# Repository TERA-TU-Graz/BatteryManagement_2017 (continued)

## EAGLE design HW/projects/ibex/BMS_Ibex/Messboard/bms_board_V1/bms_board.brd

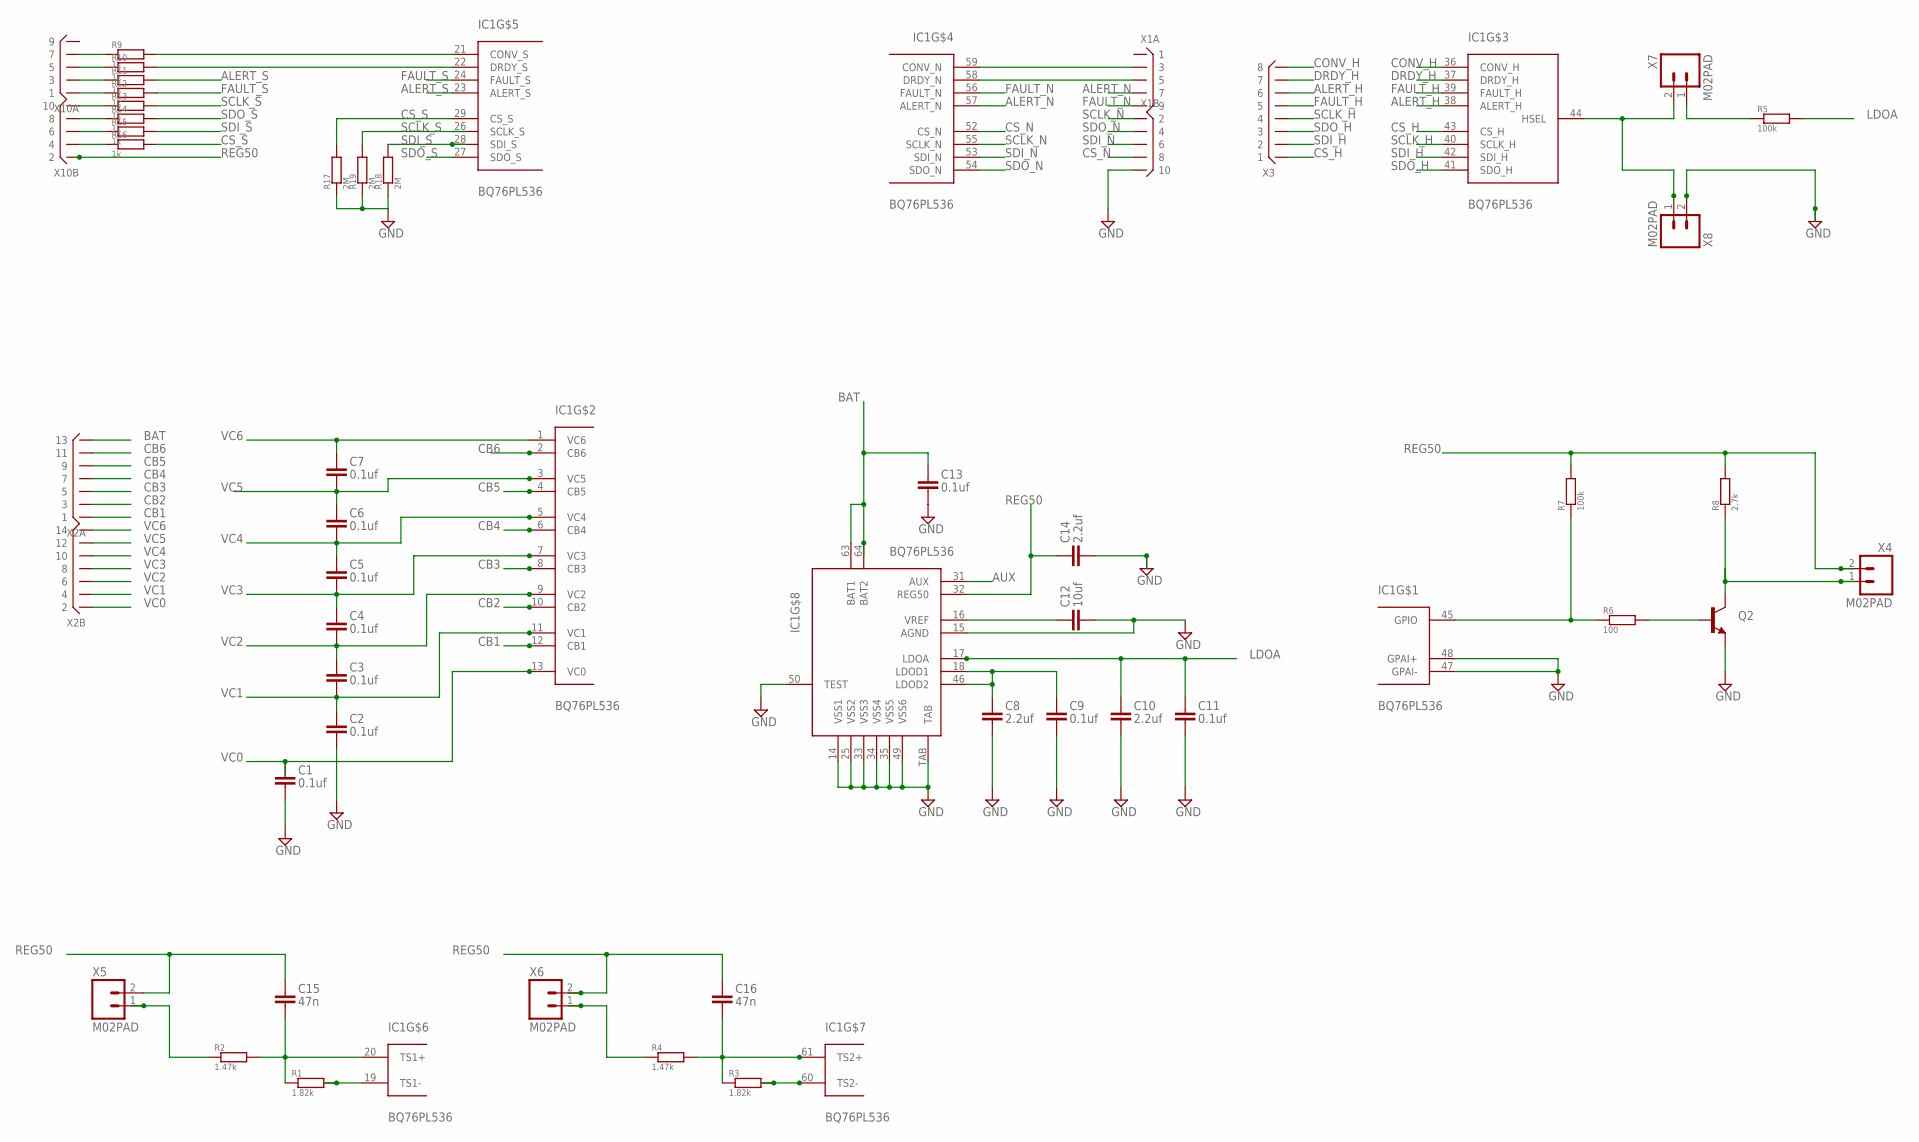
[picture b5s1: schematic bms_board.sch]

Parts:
C1, C2, C3, C4, C5, C6, C7, C9, C11, C13: 0.1uf; C0805
C8, C10, C14: 2.2uf; C0805
C12: 10uf; C0805
C15, C16: 47n; C0805
IC1: BQ76PL536; LQFP-64
Q2: TRANSISTOR_NPNSOT23; SOT23
R1, R3: 1.82k; R0805
R2, R4: 1.47k; R0805
R5, R7: 100k; R0805
R6: 100; R0805
R8: 2.7k; R0805
R9, R10, R11, R12, R13, R14, R15, R16: 1k; R0805
R17, R18, R19: 2M; R0805
X1, X10: X05X2ICR; X10ICR
X2: X07X2IR; X14R-IDC
X3: X08R; X08R-SIL
X4, X5, X6, X7, X8: M02PAD; 1X02

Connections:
ALERT_H: IC1.38 (ALERT_H), X3.6
ALERT_N: IC1.57 (ALERT_N), X1.7
ALERT_S: IC1.23 (ALERT_S), R11.2
AUX: IC1.31 (AUX)
BAT: C13.2, IC1.63 (BAT1), IC1.64 (BAT2), X2.13
CB1: IC1.12 (CB1), X2.1
CB2: IC1.10 (CB2), X2.3
CB3: IC1.8 (CB3), X2.5
CB4: IC1.6 (CB4), X2.7
CB5: IC1.4 (CB5), X2.9
CB6: IC1.2 (CB6), X2.11
CONV_H: IC1.36 (CONV_H), X3.8
CONV_N: IC1.59 (CONV_N), X1.3
CONV_S: IC1.21 (CONV_S), R9.2
CS_H: IC1.43 (CS_H), X3.1
CS_N: IC1.52 (CS_N), X1.8
CS_S: IC1.29 (CS_S), R16.2, R17.2
DRDY_H: IC1.37 (DRDY_H), X3.7
DRDY_N: IC1.58 (DRDY_N), X1.5
DRDY_S: IC1.22 (DRDY_S), R10.2
FAULT_H: IC1.39 (FAULT_H), X3.5
FAULT_N: IC1.56 (FAULT_N), X1.9
FAULT_S: IC1.24 (FAULT_S), R12.2
GND: C1.1, C2.1, C8.1, C9.1, C10.1, C11.1, C12.1, C13.1, C14.1, IC1.14 (VSS1), IC1.15 (AGND), IC1.25 (VSS2), IC1.33 (VSS3), IC1.34 (VSS4), IC1.35 (VSS5), IC1.47 (GPAI-), IC1.48 (GPAI+), IC1.49 (VSS6), IC1.50 (TEST), IC1.TAB, Q2.2 (E), R17.1, R18.1, R19.1, X1.10, X8.2
LDOA: C10.2, C11.2, IC1.17 (LDOA), R5.2
unnamed: IC1.44 (HSEL), X7.2, X8.1
unnamed: C8.2, C9.2, IC1.18 (LDOD1), IC1.46 (LDOD2)
unnamed: C12.2, IC1.16 (VREF)
unnamed: IC1.19 (TS1-), R1.2
unnamed: R2.1, X5.1
unnamed: C15.1, IC1.20 (TS1+), R1.1, R2.2
unnamed: IC1.60 (TS2-), R3.2
unnamed: C16.1, IC1.61 (TS2+), R3.1, R4.2
unnamed: R4.1, X6.1
unnamed: R5.1, X7.1
unnamed: IC1.45 (GPIO), R6.1, R7.1
unnamed: Q2.1 (B), R6.2
unnamed: Q2.3 (C), R8.1, X4.1
unnamed: R16.1, X10.4
unnamed: R15.1, X10.6
unnamed: R14.1, X10.8
unnamed: R13.1, X10.10
unnamed: R12.1, X10.1
unnamed: R11.1, X10.3
unnamed: R10.1, X10.5
unnamed: R9.1, X10.7
REG50: C14.2, C15.2, C16.2, IC1.32 (REG50), R7.2, R8.2, X4.2, X5.2, X6.2, X10.2
SCLK_H: IC1.40 (SCLK_H), X3.4
SCLK_N: IC1.55 (SCLK_N), X1.2
SCLK_S: IC1.26 (SCLK_S), R13.2, R19.2
SDI_H: IC1.42 (SDI_H), X3.2
SDI_N: IC1.53 (SDI_N), X1.6
SDI_S: IC1.28 (SDI_S), R15.2, R18.2
SDO_H: IC1.41 (SDO_H), X3.3
SDO_N: IC1.54 (SDO_N), X1.4
SDO_S: IC1.27 (SDO_S), R14.2
VC0: C1.2, IC1.13 (VC0), X2.2
VC1: C2.2, C3.1, IC1.11 (VC1), X2.4
VC2: C3.2, C4.1, IC1.9 (VC2), X2.6
VC3: C4.2, C5.1, IC1.7 (VC3), X2.8
VC4: C5.2, C6.1, IC1.5 (VC4), X2.10
VC5: C6.2, C7.1, IC1.3 (VC5), X2.12
VC6: C7.2, IC1.1 (VC6), X2.14

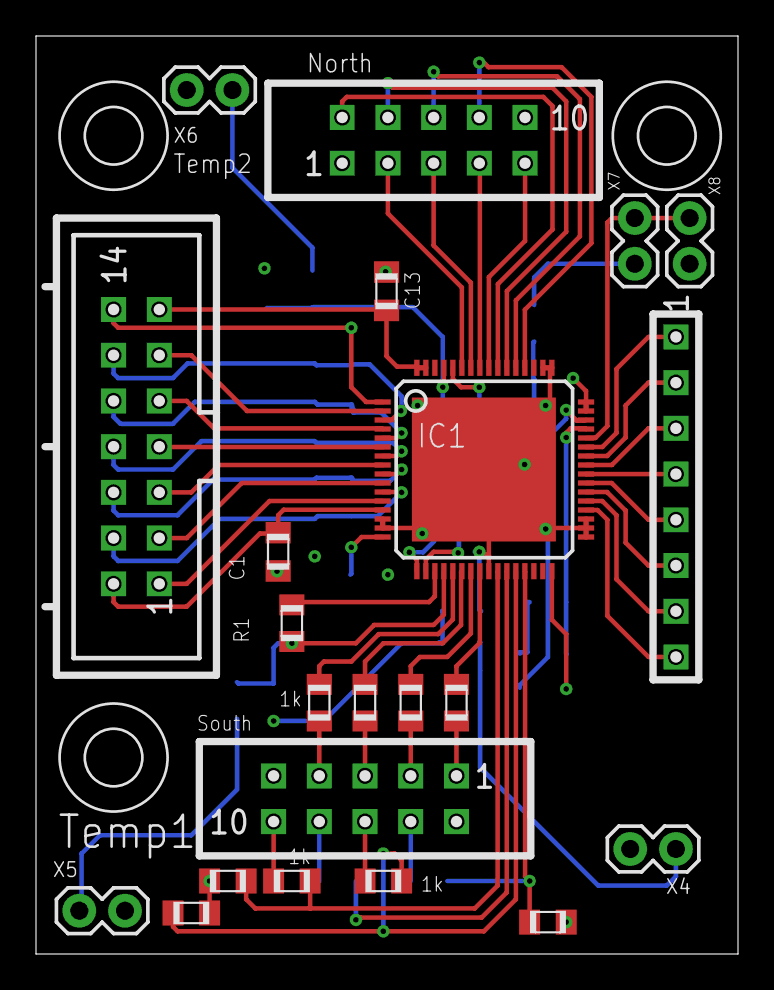
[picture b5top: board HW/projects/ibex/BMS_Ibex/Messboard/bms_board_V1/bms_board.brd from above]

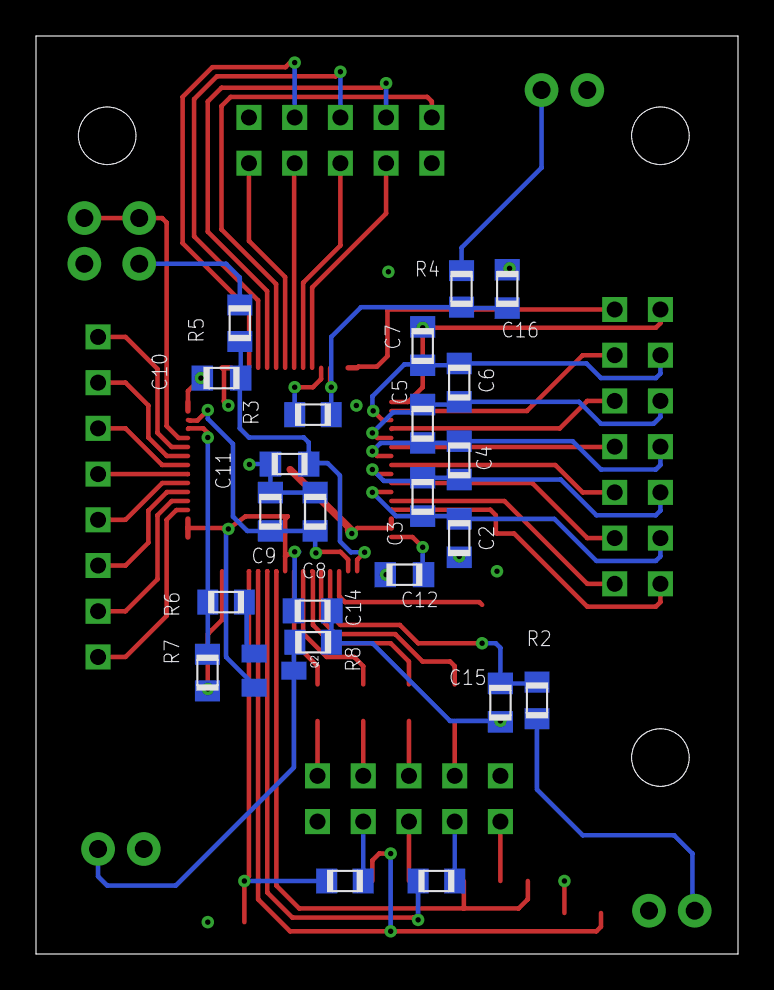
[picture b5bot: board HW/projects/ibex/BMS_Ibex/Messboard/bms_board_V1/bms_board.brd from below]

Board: 4 copper layers, 39.0 x 51.0 mm, 49 parts (24 on the bottom side), 62 nets.

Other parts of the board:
U$3, U$4, U$6: 3,2

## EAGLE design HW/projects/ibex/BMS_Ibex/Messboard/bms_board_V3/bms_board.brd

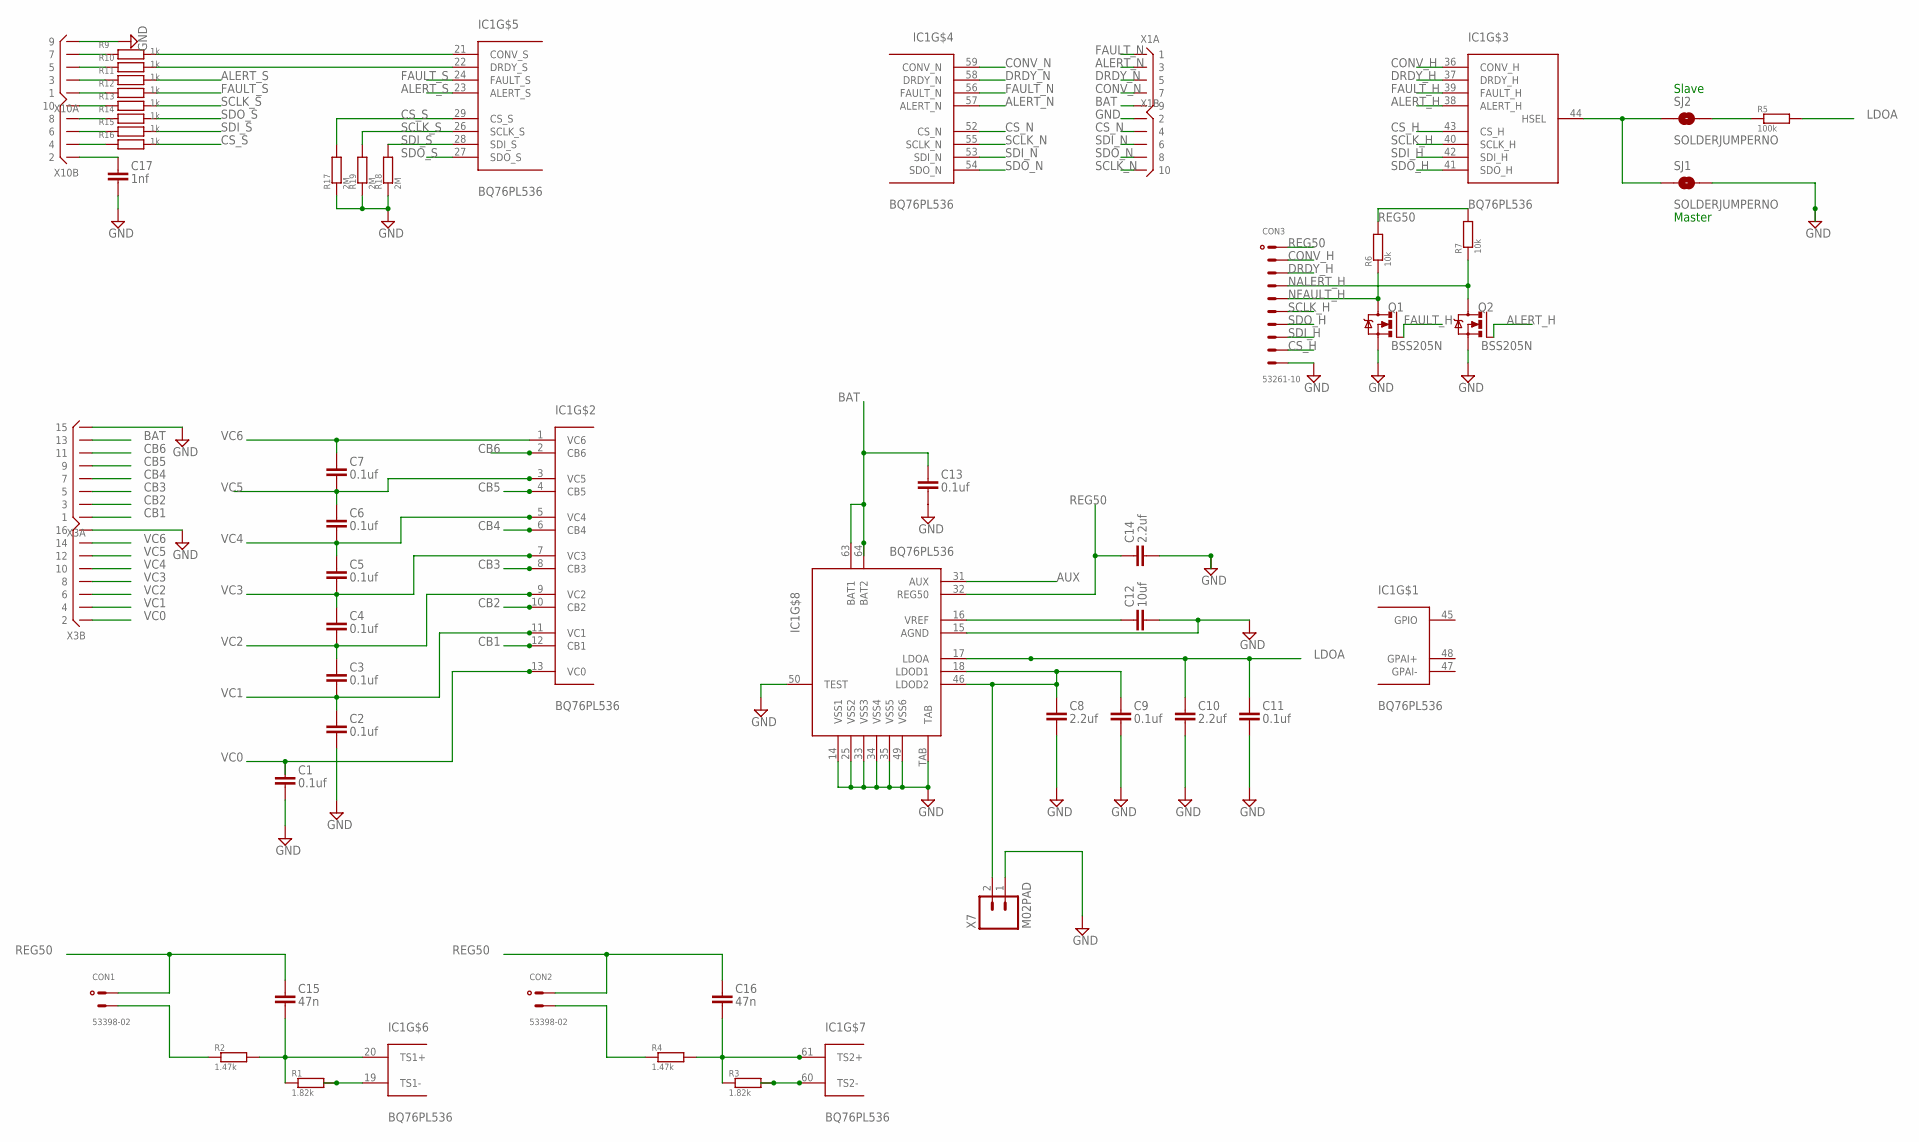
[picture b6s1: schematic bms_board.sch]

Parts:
C1, C2, C3, C4, C5, C6, C7, C9, C11, C13: 0.1uf; C0805
C8, C10, C14: 2.2uf; C0805
C12: 10uf; C0805
C15, C16: 47n; C0805
C17: 1nf; C0805
CON1, CON2: 53398-02
CON3: 53261-10
IC1: BQ76PL536; LQFP-64
Q1, Q2: BSS205N; SOT23
R1, R3: 1.82k; R0805
R2, R4: 1.47k; R0805
R5: 100k; R0805
R6, R7: 10k; R0805
R9, R10, R11, R12, R13, R14, R15, R16: 1k; R0805
R17, R18, R19: 2M; R0805
SJ1, SJ2: SOLDERJUMPERNO; SJ_2S-NO
X1, X10: X05X2ICR; X10ICR
X3: X08X2DR; X16R-DIL
X7: M02PAD; 1X02

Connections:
ALERT_H: IC1.38 (ALERT_H), Q2.1 (G)
ALERT_N: IC1.57 (ALERT_N), X1.3
ALERT_S: IC1.23 (ALERT_S), R11.2
AUX: IC1.31 (AUX)
BAT: C13.2, IC1.63 (BAT1), IC1.64 (BAT2), X1.9, X3.13
CB1: IC1.12 (CB1), X3.1
CB2: IC1.10 (CB2), X3.3
CB3: IC1.8 (CB3), X3.5
CB4: IC1.6 (CB4), X3.7
CB5: IC1.4 (CB5), X3.9
CB6: IC1.2 (CB6), X3.11
CONV_H: CON3.2, IC1.36 (CONV_H)
CONV_N: IC1.59 (CONV_N), X1.7
CONV_S: IC1.21 (CONV_S), R9.2
CS_H: CON3.9, IC1.43 (CS_H)
CS_N: IC1.52 (CS_N), X1.4
CS_S: IC1.29 (CS_S), R16.2, R17.2
DRDY_H: CON3.3, IC1.37 (DRDY_H)
DRDY_N: IC1.58 (DRDY_N), X1.5
DRDY_S: IC1.22 (DRDY_S), R10.2
FAULT_H: IC1.39 (FAULT_H), Q1.1 (G)
FAULT_N: IC1.56 (FAULT_N), X1.1
FAULT_S: IC1.24 (FAULT_S), R12.2
GND: C1.1, C2.1, C8.1, C9.1, C10.1, C11.1, C12.1, C13.1, C14.1, C17.1, CON3.10, IC1.14 (VSS1), IC1.15 (AGND), IC1.25 (VSS2), IC1.33 (VSS3), IC1.34 (VSS4), IC1.35 (VSS5), IC1.49 (VSS6), IC1.50 (TEST), IC1.TAB, Q1.2 (S), Q2.2 (S), R17.1, R18.1, R19.1, SJ1.2, X1.2, X3.15, X3.16, X7.1, X10.9
LDOA: C10.2, C11.2, IC1.17 (LDOA), R5.2
unnamed: IC1.44 (HSEL), SJ1.1, SJ2.1
unnamed: C8.2, C9.2, IC1.18 (LDOD1), IC1.46 (LDOD2), X7.2
unnamed: C12.2, IC1.16 (VREF)
unnamed: IC1.19 (TS1-), R1.2
unnamed: CON1.2, R2.1
unnamed: C15.1, IC1.20 (TS1+), R1.1, R2.2
unnamed: IC1.60 (TS2-), R3.2
unnamed: C16.1, IC1.61 (TS2+), R3.1, R4.2
unnamed: CON2.2, R4.1
unnamed: R5.1, SJ2.2
unnamed: R16.1, X10.4
unnamed: R15.1, X10.6
unnamed: R14.1, X10.8
unnamed: R13.1, X10.10
unnamed: R12.1, X10.1
unnamed: R11.1, X10.3
unnamed: R10.1, X10.5
unnamed: R9.1, X10.7
unnamed: C17.2, X10.2
NALERT_H: CON3.4, Q2.3 (D), R7.1
NFAULT_H: CON3.5, Q1.3 (D), R6.1
REG50: C14.2, C15.2, C16.2, CON1.1, CON2.1, CON3.1, IC1.32 (REG50), R6.2, R7.2
SCLK_H: CON3.6, IC1.40 (SCLK_H)
SCLK_N: IC1.55 (SCLK_N), X1.10
SCLK_S: IC1.26 (SCLK_S), R13.2, R19.2
SDI_H: CON3.8, IC1.42 (SDI_H)
SDI_N: IC1.53 (SDI_N), X1.6
SDI_S: IC1.28 (SDI_S), R15.2, R18.2
SDO_H: CON3.7, IC1.41 (SDO_H)
SDO_N: IC1.54 (SDO_N), X1.8
SDO_S: IC1.27 (SDO_S), R14.2
VC0: C1.2, IC1.13 (VC0), X3.2
VC1: C2.2, C3.1, IC1.11 (VC1), X3.4
VC2: C3.2, C4.1, IC1.9 (VC2), X3.6
VC3: C4.2, C5.1, IC1.7 (VC3), X3.8
VC4: C5.2, C6.1, IC1.5 (VC4), X3.10
VC5: C6.2, C7.1, IC1.3 (VC5), X3.12
VC6: C7.2, IC1.1 (VC6), X3.14

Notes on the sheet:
Master
Slave

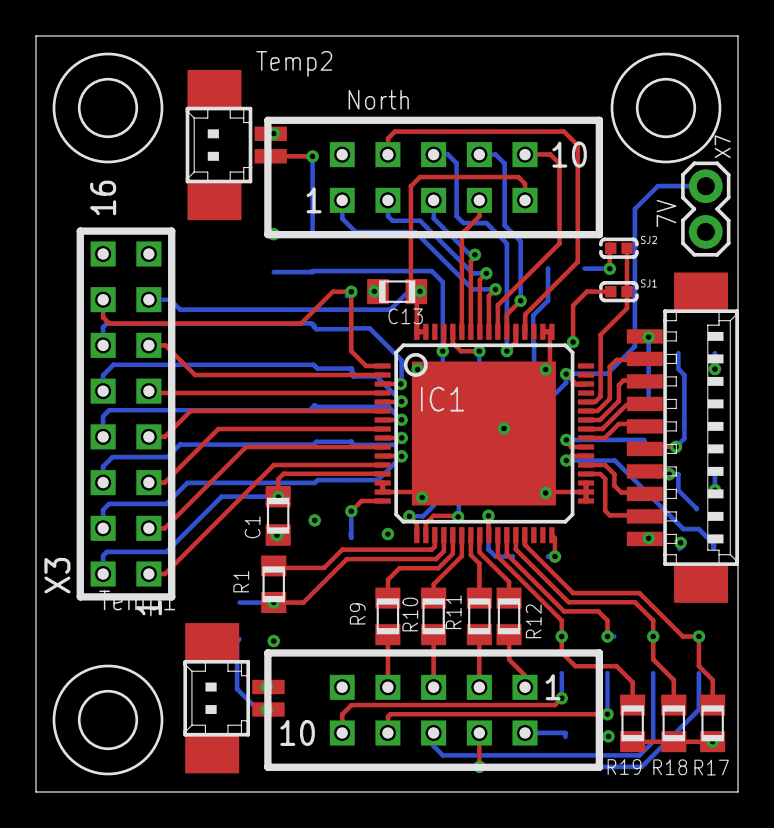
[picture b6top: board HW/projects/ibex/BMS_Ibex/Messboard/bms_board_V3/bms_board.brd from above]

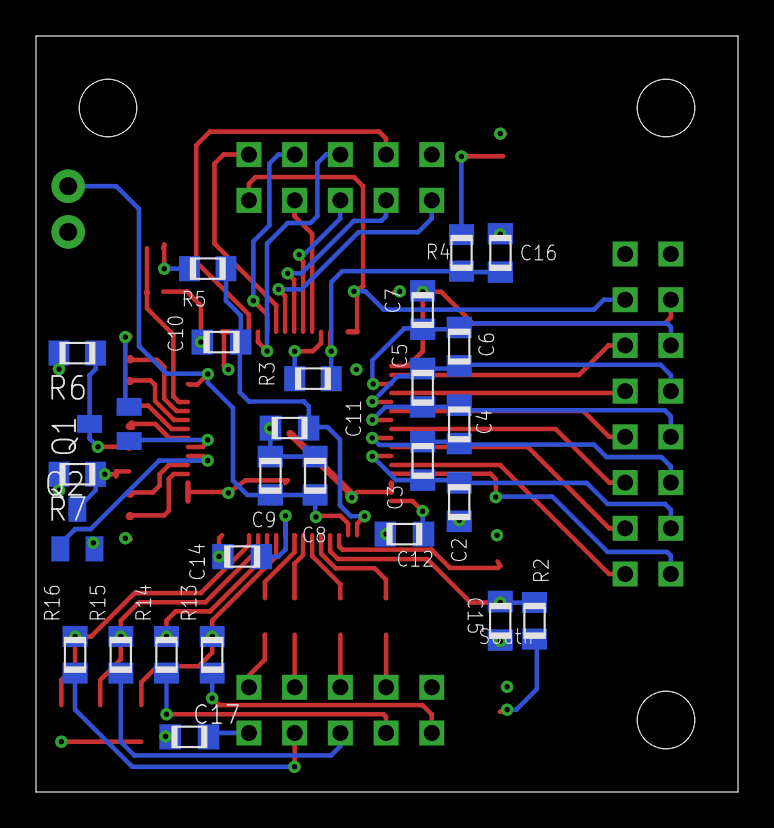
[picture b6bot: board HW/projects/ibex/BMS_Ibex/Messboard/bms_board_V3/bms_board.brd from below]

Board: 4 copper layers, 39.0 x 42.0 mm, 50 parts (27 on the bottom side), 62 nets.

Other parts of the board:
U$3, U$4, U$6: 3,2
